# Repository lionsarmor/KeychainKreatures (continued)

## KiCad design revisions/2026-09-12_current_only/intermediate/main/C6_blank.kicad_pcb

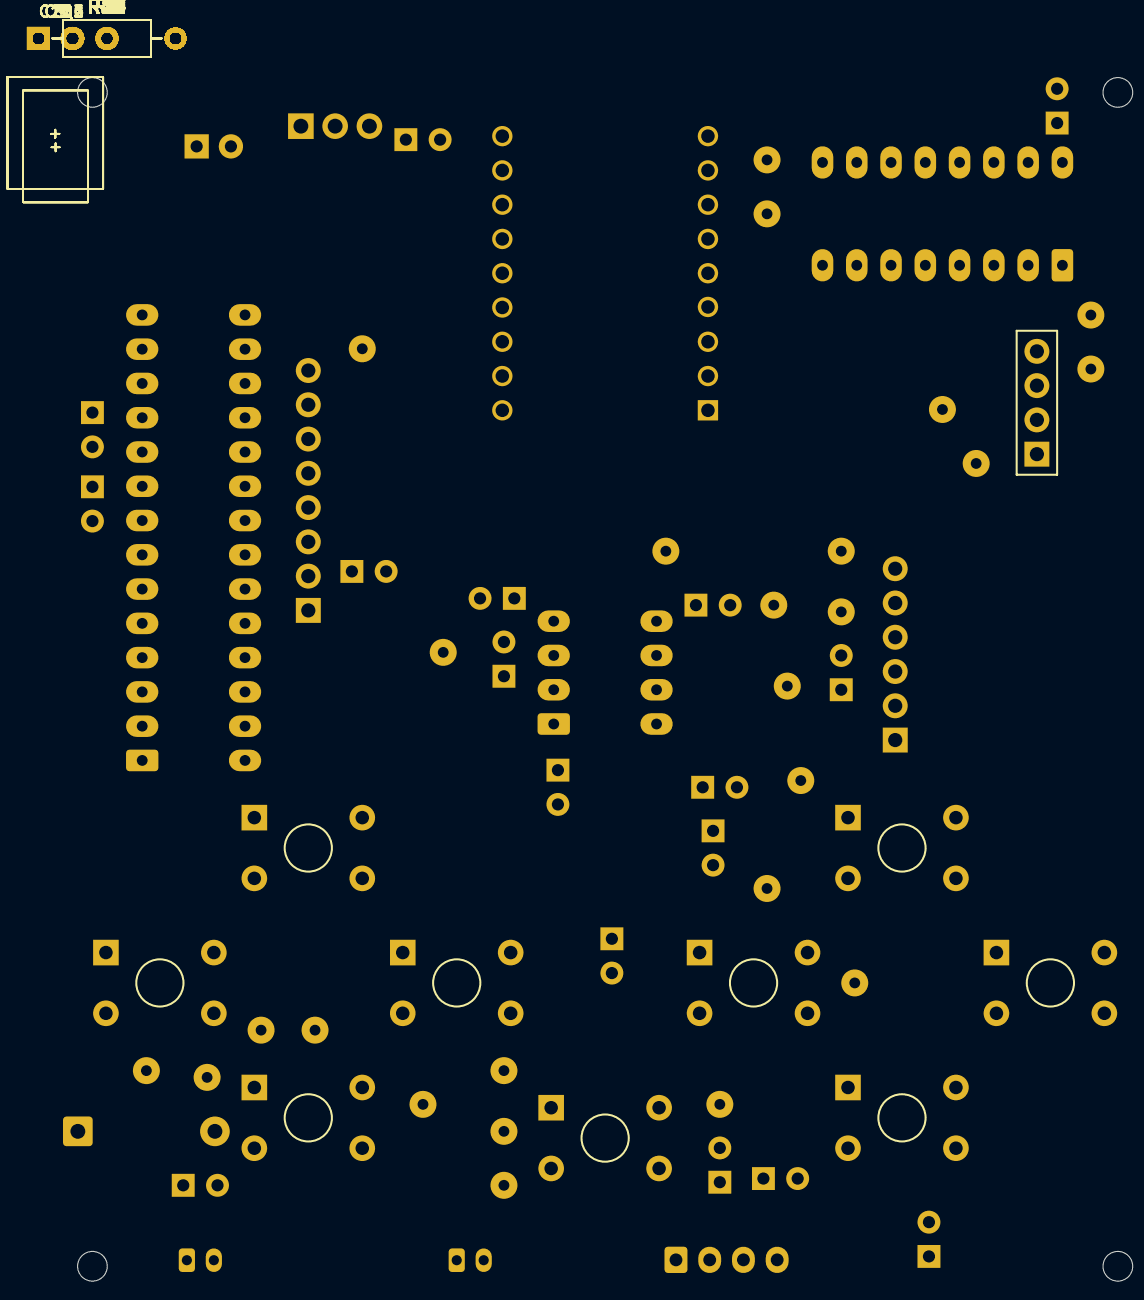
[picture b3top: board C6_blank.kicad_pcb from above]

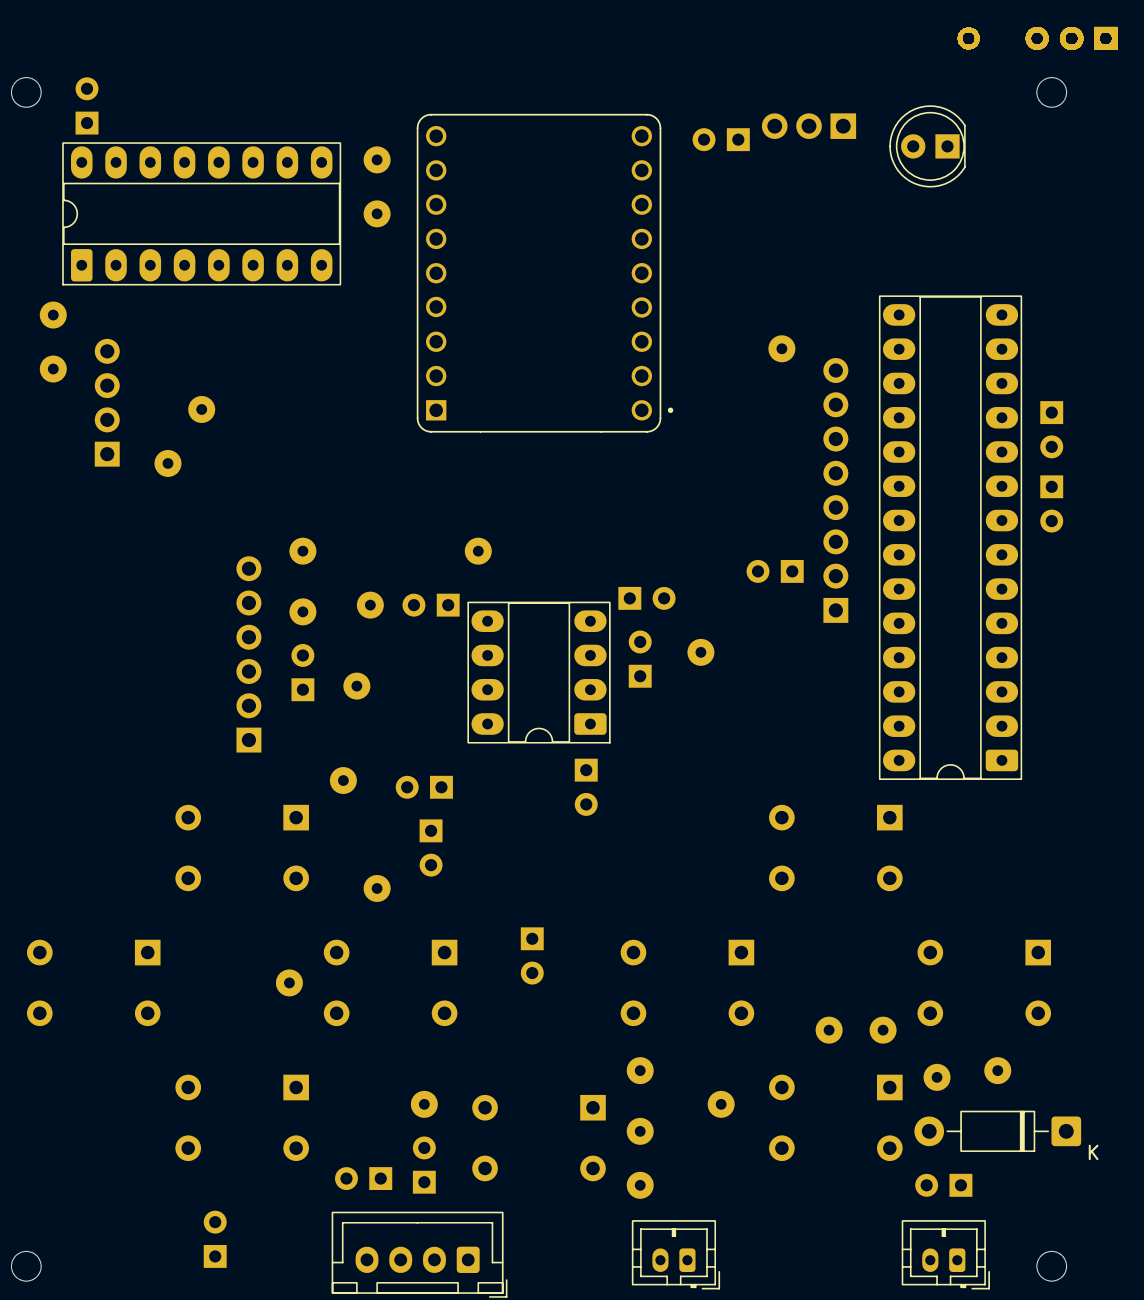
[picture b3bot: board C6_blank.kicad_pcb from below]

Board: 2 copper layers, 127 parts (57 on the bottom side), 63 nets, no tracks yet.

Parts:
C1, C3, C5, C13, C17, C25: 100u; KA_100u_Flat
C2, C4, C6, C7, C8, C10, C12, C14, C16, C23, C24, C26, C27: 100n; KEMET_C315_P2p54
C9, C11, C15, C21: 10u; KA_10u_Flat
C18, C19, C22: 10n; KEMET_C315_P2p54
C20: 1u; KEMET_C315_P2p54
D1: TSAL6200; TSAL6200_C5_EdgeFormed
D2: 1N5819; 1N5819_DO41
D3: RGB mood / common anode; RGB_CA_5mm_Socketed
H1, H2, H3, H4: M2 2.2mm NPTH
J1: SYS_IN / JST-XH; JST_XH_B4B_4
J2: XIITIA TFT header; Sullins_PPTC081_LFB
J3: GODIYMODULES SD; Sullins_PPTC061_LFB
J4: LCM0827A3038F motor; JST_PH_B2B_2
J5: 8 ohm speaker; JST_PH_B2B_2
MOD1: ESP32-S3 SuperMini; ESP32-S3-SuperMini
Q1, Q2: KSP2222ABU; TO92_Flat_P2p54
Q3: BC32725BU; TO92_Flat_P2p54
Q4, Q5: TN0702N3-G; TO92_Flat_P2p54
Q6: LP0701N3-G; TO92_Flat_P2p54
R1, R2, R19: 4.7k; MFR25_10p16
R3, R4, R5, R6, R7, R8, R9, R10, R11, R12, R13, R14, R15, R16, R17, R18, R41: 10k; MFR25_10p16
R20, R22, R26, R29, R32, R37, R39, R42, R43: 100k; MFR25_10p16
R21: 220; MFR25_10p16
R23, R24, R27, R28: 100; MFR25_10p16
R25, R30, R31, R33, R36, R38: 1k; MFR25_10p16
R34, R35: 4.7; MFR25_10p16
R40: 1.8k; MFR25_10p16
SW1: UP; Adafruit3101_ABCD
SW2: DOWN; Adafruit3101_ABCD
SW3: LEFT; Adafruit3101_ABCD
SW4: RIGHT; Adafruit3101_ABCD
SW5: A; Adafruit3101_ABCD
SW6: B; Adafruit3101_ABCD
SW7: X; Adafruit3101_ABCD
SW8: Y; Adafruit3101_ABCD
SW9: FN; Adafruit3101_ABCD
TP1: 5V; Debug_PTH_2mm
TP2: 3V3; Debug_PTH_2mm
TP3: 3V2; Debug_PTH_2mm
TP4: GND-P; Debug_PTH_2mm
TP6: GND-A; Debug_PTH_2mm
TP8: GND-M; Debug_PTH_2mm
TP9: SDA; Debug_PTH_2mm
TP10: SCL; Debug_PTH_2mm
TP11: KEY-IRQ; Debug_PTH_2mm
TP12: FN; Debug_PTH_2mm
TP13: SCK; Debug_PTH_2mm
TP14: MOSI; Debug_PTH_2mm
TP16: SD-CS; Debug_PTH_2mm
TP17: TFT-CS; Debug_PTH_2mm
TP18: TFT-DC; Debug_PTH_2mm
TP19: TFT-RST; Debug_PTH_2mm
TP20: BL-PWM; Debug_PTH_2mm
TP21: BLK; Debug_PTH_2mm
TP22: AUD-PWM; Debug_PTH_2mm
TP23: AUD-LP2; Debug_PTH_2mm
TP29: MOT-RET; Debug_PTH_2mm
TP30: IR-TX; Debug_PTH_2mm
TP31: IR-RX; Debug_PTH_2mm
TP32: IR-V; Debug_PTH_2mm
TP33: IO-RST; Debug_PTH_2mm
U1: MCP23017-E/SP; ED281DT_DIP28_Socket
U2: TSOP38238; TSOP38238_Vertical
U3: TDA2822L-D08-T; ED08DT_DIP8_Socket
U4: TLC5916IN; ED16DT_DIP16_Socket

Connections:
/ACT_3V2: C5.1, C6.1, C16.1, C17.1, D2.1, J1.4, J4.1, Q6.1, R39.1, TP3.1
/AMP_EN: R36.1, U1.5
/AUDIO_PWM: MOD1.8, R30.1, TP22.1
/BL_PWM: MOD1.9, R19.1, TP20.1
/BUTTON_FN_N: MOD1.2, R13.2, SW9.A, SW9.B, TP12.1
/BUTTON_INT_N: MOD1.1, R3.2, TP11.1, U1.20
/GND: C1.2, C2.2, C3.2, C4.2, C5.2, C6.2, C7.2, C8.2, C9.2, C10.2, C11.2, C12.2, C13.2, C14.2, C15.2, C17.2, C18.2, C19.2, C22.2, C25.2, C26.2, C27.2, J1.2, J2.1, J3.6, MOD1.GND, Q1.1, Q2.1, Q4.1, Q5.1, R20.2, R26.2, R29.2, R33.2, R34.2, R35.2, R37.2, R40.2, R42.2, R43.2, SW1.C, SW1.D, SW2.C, SW2.D, SW3.C, SW3.D, SW4.C, SW4.D, SW5.C, SW5.D, SW6.C, SW6.D, SW7.C, SW7.D, SW8.C, SW8.D, SW9.C, SW9.D, TP4.1, TP6.1, TP8.1, U1.10, U1.15, U1.16, U1.17, U2.2, U3.4, U3.6, U4.1
/I2C_SCL: MOD1.5, R2.2, TP10.1, U1.12
/I2C_SDA: MOD1.4, R1.2, TP9.1, U1.13
/IR_RX: MOD1.6, TP31.1, U2.1
/IR_TX: MOD1.7, R25.1, TP30.1
/LOGIC_3V3: C3.1, C4.1, C8.1, C9.1, C10.1, C11.1, C12.1, C13.1, C27.1, J1.3, J2.2, J3.1, Q3.3, R1.1, R2.1, R3.1, R4.1, R5.1, R6.1, R7.1, R8.1, R9.1, R10.1, R11.1, R12.1, R13.1, R14.1, R15.1, R16.1, R17.1, R18.1, R22.1, R24.1, R27.1, R41.1, TP2.1, U1.9, U4.16
/MCU_5V: C1.1, C2.1, D3.2, J1.1, MOD1.5V, TP1.1
/MOTOR_EN: R28.1, U1.6
/RGB_CLK: R43.1, U1.26, U4.3
/RGB_DATA: R42.1, U1.25, U4.2
/RGB_LATCH: U1.27, U4.4
/RGB_OE_N: R41.2, U1.28, U4.13
/SD_CS: J3.2, MOD1.10, R15.2, TP16.1
/SPI_MISO: J3.5, MOD1.12, R18.2
/SPI_MOSI: J2.4, J3.3, MOD1.11, R17.2, TP14.1
/SPI_SCK: J2.3, J3.4, MOD1.13, TP13.1
/TFT_CS: J2.7, MOD1.RX, R14.2, TP17.1
/TFT_DC: J2.6, MOD1.TX, TP18.1
/TFT_RST_N: J2.5, R16.2, TP19.1, U1.7
unnamed: C18.1, R30.2, R31.1
unnamed: C19.1, C20.1, R31.2, TP23.1
unnamed: C20.2, R32.1
unnamed: C23.2, R34.1
unnamed: C24.2, R35.1
unnamed: D1.2, R24.2
unnamed: D1.1, Q1.3
unnamed: C16.2, D2.2, J4.2, Q4.3, TP29.1
unnamed: D3.3, U4.7
unnamed: D3.4, U4.6
unnamed: D3.1, U4.5
unnamed: J2.8, R23.2, TP21.1
unnamed: C23.1, J5.1, U3.1
unnamed: C24.1, J5.2, U3.3
unnamed: Q1.2, R25.2, R26.1
unnamed: Q2.2, R19.2, R20.1
unnamed: Q2.3, R21.2
unnamed: Q3.2, R21.1, R22.2
unnamed: Q3.1, R23.1
unnamed: Q4.2, R28.2, R29.1
unnamed: Q5.3, R38.2
unnamed: Q5.2, R36.2, R37.1
unnamed: C25.1, C26.1, Q6.3, U3.2
unnamed: Q6.2, R38.1, R39.2
unnamed: R5.2, SW1.A, SW1.B, U1.21
unnamed: R6.2, SW2.A, SW2.B, U1.22
unnamed: R7.2, SW3.A, SW3.B, U1.23
unnamed: R8.2, SW4.A, SW4.B, U1.24
unnamed: R9.2, SW5.A, SW5.B, U1.1
unnamed: R10.2, SW6.A, SW6.B, U1.2
unnamed: R11.2, SW7.A, SW7.B, U1.3
unnamed: R12.2, SW8.A, SW8.B, U1.4
unnamed: C7.1, R4.2, TP33.1, U1.18
unnamed: C14.1, C15.1, R27.2, TP32.1, U2.3
unnamed: R32.2, R33.1, U3.7
unnamed: C21.1, U3.8
unnamed: C21.2, C22.1, U3.5
unnamed: R40.1, U4.15

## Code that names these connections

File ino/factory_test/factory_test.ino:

/*
  Keychain Kreatures Factory Test
  ESP32-C3 Super Mini
*/

#include <Arduino.h>
#include <Wire.h>
#include <Adafruit_GFX.h>
#include <Adafruit_ST7789.h>
#include "driver/i2s.h"
#include <math.h>

// Display
#define TFT_SCLK 4
#define TFT_MOSI 6
#define TFT_RST  7
#define TFT_DC   2
#define TFT_CS   10
Adafruit_ST7789 tft(TFT_CS, TFT_DC, TFT_MOSI, TFT_SCLK, TFT_RST);

// Audio
#define I2S_DIN   20
#define I2S_BCLK  21
#define I2S_LRC   0
#define AMP_SD    5
#define I2S_PORT  I2S_NUM_0

// PCF8574
#define PCF_ADDR 0x20
#define I2C_SDA  8
#define I2C_SCL  9
#define BTN_UP    0
#define BTN_DOWN  1
#define BTN_LEFT  2
#define BTN_RIGHT 3
#define BTN_A     4
#define BTN_B     5
#define BTN_P6    6
#define IR_RX_P7  7

// IR + vibration
#define IR_TX_PIN 1
#define VIBE_PIN  3

uint8_t lastState = 0xFF;
bool pcfOK = false;
int logY = 116;
unsigned long lastIrMs = 0;

void logLine(const String &s, uint16_t color = ST77XX_WHITE) {
  Serial.println(s);
  if (logY > 264) {
    tft.fillRect(0, 112, 240, 168, ST77XX_BLACK);
    logY = 116;
  }
  tft.setTextSize(1);
  tft.setTextColor(color, ST77XX_BLACK);
  tft.setCursor(6, logY);
  tft.println(s);
  logY += 13;
}

void drawUI() {
  tft.fillScreen(ST77XX_BLACK);
  tft.setTextSize(2);
  tft.setTextColor(ST77XX_CYAN);
  tft.setCursor(8, 8);
  tft.println("KEYCHAIN");
  tft.setCursor(8, 31);
  tft.println("KREATURES");

  tft.setTextSize(1);
  tft.setTextColor(ST77XX_WHITE);
  tft.setCursor(8, 60);
  tft.println("FACTORY TEST");

  tft.drawLine(0, 76, 239, 76, ST77XX_BLUE);
  tft.setCursor(8, 83);
  tft.setTextColor(ST77XX_ORANGE);
  tft.print("A = VIBRATE");
  tft.setCursor(112, 83);
  tft.setTextColor(ST77XX_MAGENTA);
  tft.print("B = IR TX");

  tft.setCursor(8, 99);
  tft.setTextColor(pcfOK ? ST77XX_GREEN : ST77XX_RED);
  tft.print(pcfOK ? "PCF8574 OK" : "PCF8574 FAIL");
}

bool detectPCF() {
  Wire.beginTransmission(PCF_ADDR);
  return Wire.endTransmission() == 0;
}

void releasePCFPins() {
  Wire.beginTransmission(PCF_ADDR);
  Wire.write(0xFF);
  Wire.endTransmission();
}

uint8_t readPCF() {
  Wire.requestFrom(PCF_ADDR, 1);
  return Wire.available() ? Wire.read() : 0xFF;
}

bool setupAudio() {
  pinMode(AMP_SD, OUTPUT);
  digitalWrite(AMP_SD, HIGH);

  i2s_config_t cfg = {
    .mode = i2s_mode_t(I2S_MODE_MASTER | I2S_MODE_TX),
    .sample_rate = 22050,
    .bits_per_sample = I2S_BITS_PER_SAMPLE_16BIT,
    .channel_format = I2S_CHANNEL_FMT_RIGHT_LEFT,
    .communication_format = I2S_COMM_FORMAT_STAND_I2S,
    .intr_alloc_flags = ESP_INTR_FLAG_LEVEL1,
    .dma_buf_count = 8,
    .dma_buf_len = 128,
    .use_apll = false,
    .tx_desc_auto_clear = true,
    .fixed_mclk = 0
  };

  i2s_pin_config_t pins = {
    .bck_io_num = I2S_BCLK,
    .ws_io_num = I2S_LRC,
    .data_out_num = I2S_DIN,
    .data_in_num = I2S_PIN_NO_CHANGE
  };

  esp_err_t e = i2s_driver_install(I2S_PORT, &cfg, 0, nullptr);
  if (e != ESP_OK && e != ESP_ERR_INVALID_STATE) return false;
  return i2s_set_pin(I2S_PORT, &pins) == ESP_OK;
}

void toneOut(int frequency, int durationMs, int amplitude = 15000) {
  const int sampleRate = 22050;
  const int framesTotal = sampleRate * durationMs / 1000;
  const int chunk = 64;
  int16_t buffer[chunk * 2];

  for (int made = 0; made < framesTotal; ) {
    int count = min(chunk, framesTotal - made);
    for (int i = 0; i < count; i++) {
      float phase = 2.0f * PI * frequency * (made + i) / sampleRate;
      int16_t sample = (int16_t)(sinf(phase) * amplitude);
      buffer[i * 2] = sample;
      buffer[i * 2 + 1] = sample;
    }
    size_t written = 0;
    i2s_write(I2S_PORT, buffer, count * 4, &written, portMAX_DELAY);
    made += count;
  }
}

void vibrate(unsigned long ms) {
  logLine("VIBRATOR ON", ST77XX_ORANGE);
  digitalWrite(VIBE_PIN, HIGH);
  delay(ms);
  digitalWrite(VIBE_PIN, LOW);
  logLine("VIBRATOR OFF", ST77XX_ORANGE);
}

void irMark(unsigned int us) {
  unsigned long start = micros();
  while ((unsigned long)(micros() - start) < us) {
    digitalWrite(IR_TX_PIN, HIGH);
    delayMicroseconds(13);
    digitalWrite(IR_TX_PIN, LOW);
    delayMicroseconds(13);
  }
}

void irSpace(unsigned int us) {
  digitalWrite(IR_TX_PIN, LOW);
  delayMicroseconds(us);
}

void sendIR() {
  logLine("IR TX START", ST77XX_MAGENTA);
  irMark(9000);
  irSpace(4500);
  for (int i = 0; i < 16; i++) {
    irMark(560);
    irSpace((i & 1) ? 1690 : 560);
  }
  irMark(560);
  digitalWrite(IR_TX_PIN, LOW);
  logLine("IR TX DONE", ST77XX_MAGENTA);
}

void handlePress(uint8_t pin) {
  static const int tones[7] = {520, 440, 600, 700, 820, 980, 300};

  switch (pin) {
    case BTN_UP:    logLine("BUTTON UP", ST77XX_YELLOW); break;
    case BTN_DOWN:  logLine("BUTTON DOWN", ST77XX_YELLOW); break;
    case BTN_LEFT:  logLine("BUTTON LEFT", ST77XX_YELLOW); break;
    case BTN_RIGHT: logLine("BUTTON RIGHT", ST77XX_YELLOW); break;
    case BTN_A:     logLine("BUTTON A", ST77XX_ORANGE); break;
    case BTN_B:     logLine("BUTTON B", ST77XX_MAGENTA); break;
    case BTN_P6:    logLine("PCF P6 ACTIVE", ST77XX_YELLOW); break;
  }

  toneOut(tones[pin], 70);

  if (pin == BTN_A) vibrate(300);
  if (pin == BTN_B) sendIR();
}

void processPCF(uint8_t state) {
  uint8_t changed = state ^ lastState;

  for (uint8_t pin = 0; pin <= 6; pin++) {
    if (bitRead(changed, pin) && bitRead(state, pin) == LOW) {
      handlePress(pin);
    }
  }

  if (bitRead(changed, IR_RX_P7) &&
      bitRead(state, IR_RX_P7) == LOW &&
      millis() - lastIrMs > 120) {
    lastIrMs = millis();
    logLine("IR RX ACTIVITY", ST77XX_GREEN);
    toneOut(350, 70);
    toneOut(700, 90);
  }

  lastState = state;
}

void setup() {
  Serial.begin(115200);
  delay(400);

  pinMode(VIBE_PIN, OUTPUT);
  digitalWrite(VIBE_PIN, LOW);

  pinMode(IR_TX_PIN, OUTPUT);
  digitalWrite(IR_TX_PIN, LOW);

  Wire.begin(I2C_SDA, I2C_SCL);
  Wire.setClock(100000);

  pcfOK = detectPCF();
  if (pcfOK) {
    releasePCFPins();
    delay(5);
    lastState = readPCF();
  }

  tft.init(240, 280);
  tft.setRotation(0);
  drawUI();

  bool audioOK = setupAudio();

  logLine("DISPLAY OK", ST77XX_GREEN);
  logLine(pcfOK ? "PCF8574 OK" : "PCF8574 FAIL",
          pcfOK ? ST77XX_GREEN : ST77XX_RED);
  logLine(audioOK ? "AUDIO TEST" : "AUDIO INIT FAIL",
          audioOK ? ST77XX_GREEN : ST77XX_RED);

  if (audioOK) {
    toneOut(440, 90);
    toneOut(660, 90);
    toneOut(880, 130);
  }

  vibrate(250);
  logLine("READY", ST77XX_CYAN);
}

void loop() {
  if (pcfOK) {
    processPCF(readPCF());
  }
  delay(2);
}

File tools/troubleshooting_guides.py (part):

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9:'eFuse current-programming node; no universal digital level.',10:'Active-low eFuse fault; pull-up is to SYS_RAW, not fixed 3.3 V.',
11:'Regulator status, pulled toward REG_3V3; not independent supervisor output.',12:'Common output-gate enable; high after valid supervision.',
13:'Pre-gate 5 V regulator output.',14:'Pre-gate 3.3 V regulator output.',15:'Pre-gate 3.2 V regulator output.',
16:'Gated MCU_5V to J3 pin 1.',17:'Gated LOGIC_3V3 to J3 pin 3.',18:'Gated ACT_3V2 to J3 pin 4.',
19:'Analog thermistor node; depends on source and sensor. No forced logic levels.',
20:'CC-mode OUT1: high for default, low for 1.5/3 A attached advertisement.',
21:'Inverted mode control: low default, high for 1.5/3 A advertisement.',22:'USB supply after U13 current limiter, before charger.',
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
